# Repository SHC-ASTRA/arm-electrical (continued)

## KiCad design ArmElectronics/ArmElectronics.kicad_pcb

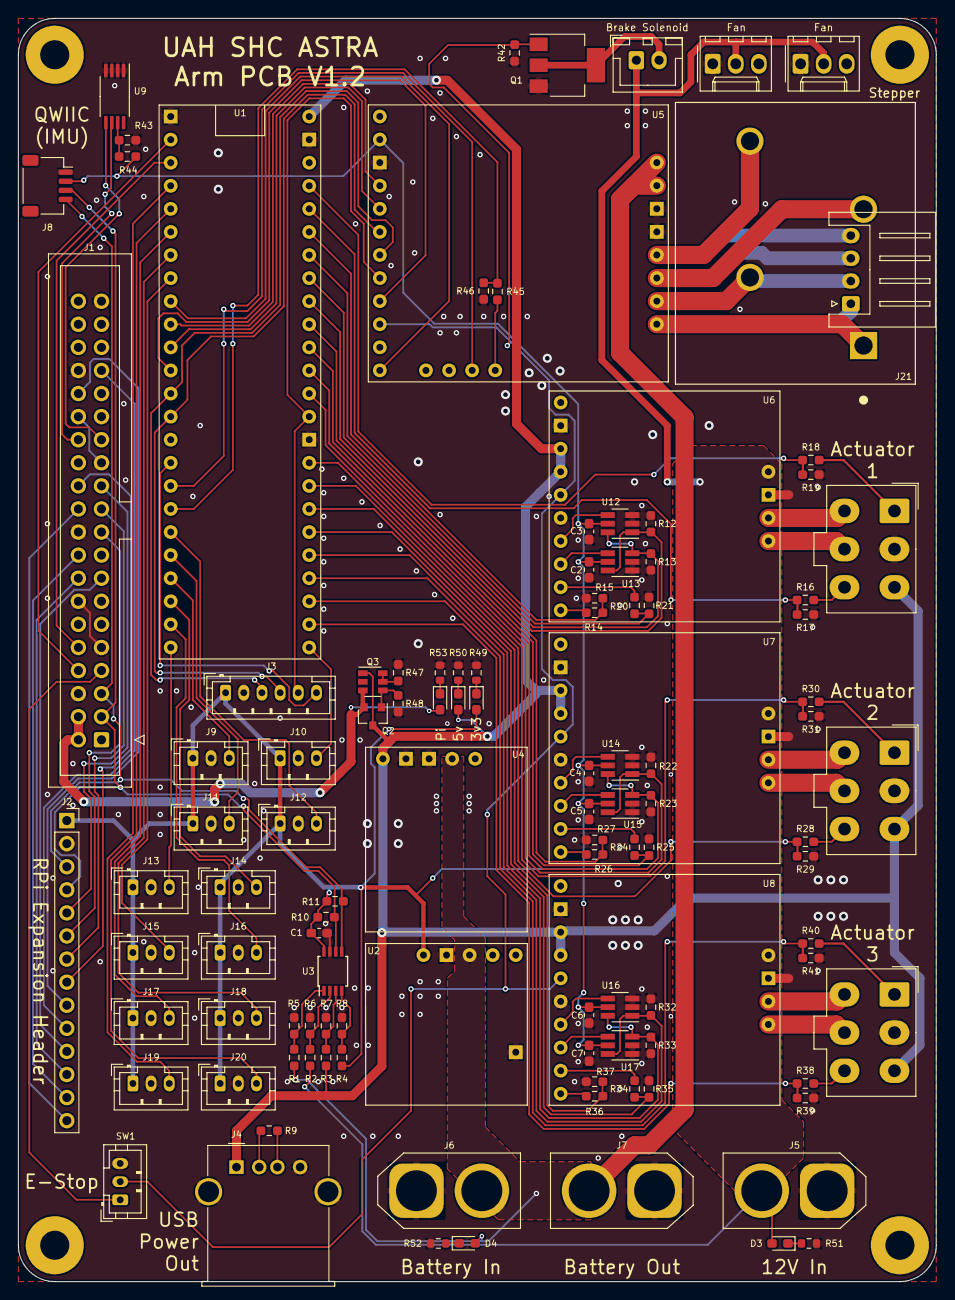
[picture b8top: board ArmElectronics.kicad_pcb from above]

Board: 2 copper layers, 101.0 x 139.0 mm, 116 parts (0 on the bottom side), 108 nets.

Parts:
C1, C2, C3, C4, C5, C6, C7: 0.1u; C_0603_1608Metric_Pad1.05x0.95mm_HandSolder
D1, D2, D3, D4, D5: G; LED_0603_1608Metric_Pad1.05x0.95mm_HandSolder
H1, H2, H3, H4: MountingHole; MountingHole_3.2mm_M3_Pad
J1: Raspberry_Pi_2_3; IDC-Header_2x20_P2.54mm_Vertical
J2: Conn_01x14; PinSocket_1x14_P2.54mm_Vertical
J3: Encoder Breakout; JST_PH_B6B-PH-K_1x06_P2.00mm_Vertical
J4: RasPi Power Out; USB_A_Molex_67643_Horizontal
J5: 12V In; AMASS_XT60-F_1x02_P7.20mm_Vertical
J6: Batt In; AMASS_XT60-F_1x02_P7.20mm_Vertical
J7: Batt Out; AMASS_XT60-F_1x02_P7.20mm_Vertical
J8: BNO055 QWIIC Conn; JST_SH_SM04B-SRSS-TB_1x04-1MP_P1.00mm_Horizontal
J9, J10, J11, J12, J13, J14, J15, J16, J17, J18, J19, J20: AH1815 Breakout; JST_PH_B3B-PH-K_1x03_P2.00mm_Vertical
J21: 1792245; PHOENIX_1792245
J22, J23, J24: PA-09; Molex_Mini-Fit_Jr_5566-06A_2x03_P4.20mm_Vertical
J25: Solenoid; JST_XH_B2B-XH-A_1x02_P2.50mm_Vertical
J26: Stepper Alternate Connection; JST_XH_S4B-XH-A_1x04_P2.50mm_Horizontal
J27, J28: Computer Fan; Molex_KK-254_AE-6410-03A_1x03_P2.54mm_Vertical
Q1: Q_NMOS_GDSD; SOT-223
Q2: Q_PMOS_GSD; SOT-23
Q3: DMMT3906; SOT-23-6
R1: 240k; R_0603_1608Metric_Pad0.98x0.95mm_HandSolder
R2: 62k; R_0603_1608Metric_Pad0.98x0.95mm_HandSolder
R3, R4, R15, R17, R19, R27, R29, R31, R37, R39, R41: 20k; R_0603_1608Metric_Pad0.98x0.95mm_HandSolder
R5, R6, R7, R8, R14, R16, R18, R20, R21, R24, R25, R26, R28, R30, R34, R35, R36, R38, R40, R44, R45, R46, R47: 10k; R_0603_1608Metric_Pad0.98x0.95mm_HandSolder
R9: 200; R_0603_1608Metric_Pad0.98x0.95mm_HandSolder
R10, R11, R12, R13, R22, R23, R32, R33, R42: 100k; R_0603_1608Metric_Pad0.98x0.95mm_HandSolder
R43: DNP; R_0603_1608Metric_Pad0.98x0.95mm_HandSolder
R48: 47k; R_0603_1608Metric_Pad0.98x0.95mm_HandSolder
R49: 10; R_0603_1608Metric
R50, R53: 180; R_0603_1608Metric
R51: 1k; R_0603_1608Metric
R52: 3.3k; R_0603_1608Metric
SW1: E-Stop; JST_PH_B3B-PH-K_1x03_P2.00mm_Vertical
U1: Teensy4.1
U2: Pololu_2857
U3: MAX11607; TSSOP-8_3x3mm_P0.65mm
U4: Pololu_2851
U5: Pololu_3730
U6, U7, U8: TB9051FTG
U9: CAT24C32; TSSOP-8_4.4x3mm_P0.65mm
U12, U13, U14, U15, U16, U17: 74LVC1G97; SOT-23-6_Handsoldering

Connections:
+3V3: C1.2, C2.2, C3.2, C4.2, C5.2, C6.2, C7.2, D1.2, J2.1, J3.1, J8.2, J9.1, J10.1, J11.1, J12.1, J13.1, J14.1, J15.1, J16.1, J17.1, J18.1, J19.1, J20.1, R4.1, R10.2, R11.2, R44.2, U2.5, U3.8, U5.2, U12.5, U13.5, U14.5, U15.5, U16.5, U17.5
+5V: D2.2, J4.1, J22.3, J23.3, J24.3, Q2.3, Q3.1, R3.1, U1.30, U4.5, U6.3, U6.4, U7.3, U7.4, U8.3, U8.4
+12V: D3.2, J5.2, J25.1, J27.2, J28.2, R2.1, U6.15, U7.15, U8.15
+BATT: D4.2, J6.2, J7.2, R1.1, U2.3, U4.2, U5.23, U5.24
/5V_RPI: D5.2, J1.2, J1.4, Q2.2, Q3.3
/Encoder_CS: J3.6, U1.31
/Hall_SW_1: J9.3, U1.36
/Hall_SW_2: J10.3, U1.40
/Hall_SW_3: J11.3, U1.35
/Hall_SW_4: J12.3, U1.34
/Hall_SW_5: J13.3, U1.39
/Hall_SW_6: J14.3, U1.37
/Hall_SW_7: J15.3, U1.8
/Hall_SW_8: J16.3, U1.38
/Hall_SW_9: J17.3, U1.6
/Hall_SW_10: J18.3, U1.7
/Hall_SW_11: J19.3, U1.4
/Hall_SW_12: J20.3, U1.5
/ID_SCL: J1.28, U9.6
/ID_SDA: J1.27, U9.5
/M1_DIAG: R14.2, U6.10
/M1_DIAG_3v: R14.1, R15.2, U1.25
/M1_DIR: R13.2, U1.23, U12.6, U13.3
/M1_HALL1: J22.6, R16.2
/M1_HALL1_3v: R16.1, R17.2, U1.26
/M1_HALL2: J22.1, R18.2
/M1_HALL2_3v: R18.1, R19.2, U1.27
/M1_OCM: R20.2, U6.9
/M1_OCM_3v: R20.1, R21.2, U1.24
/M1_PWM: R12.2, U1.22, U12.1, U13.6
/M1_PWM1: U6.7, U12.4
/M1_PWM2: U6.8, U13.4
/M2_DIAG: R26.2, U7.10
/M2_DIAG_3v: R26.1, R27.2, U1.21
/M2_DIR: R23.2, U1.19, U14.6, U15.3
/M2_HALL1: J23.6, R28.2
/M2_HALL1_3v: R28.1, R29.2, U1.47
/M2_HALL2: J23.1, R30.2
/M2_HALL2_3v: R30.1, R31.2, U1.48
/M2_OCM: R24.2, U7.9
/M2_OCM_3v: R24.1, R25.2, U1.20
/M2_PWM: R22.2, U1.18, U14.1, U15.6
/M2_PWM1: U7.7, U14.4
/M2_PWM2: U7.8, U15.4
/M3_DIAG: R36.2, U8.10
/M3_DIAG_3v: R36.1, R37.2, U1.46
/M3_DIR: R33.2, U1.44, U16.6, U17.3
/M3_HALL1: J24.6, R38.2
/M3_HALL1_3v: R38.1, R39.2, U1.41
/M3_HALL2: J24.1, R40.2
/M3_HALL2_3v: R40.1, R41.2, U1.42
/M3_OCM: R34.2, U8.9
/M3_OCM_3v: R34.1, R35.2, U1.45
/M3_PWM: R32.2, U1.43, U16.1, U17.6
/M3_PWM1: U8.7, U16.4
/M3_PWM2: U8.8, U17.4
/Motor_Enable: J1.7, SW1.1
/RPi_CS0: J1.24, J2.8
/RPi_GPI022: J1.15, J2.11
/RPi_GPIO12: J1.32, J2.9
/RPi_GPIO13: J1.33, J2.10
/RPi_GPIO23: J1.16, J2.12
/RPi_GPIO24: J1.18, J2.13
/RPi_GPIO25: J1.22, J2.14
/RPi_MISO0: J1.21, J2.7
/RPi_MOSI0: J1.19, J2.6
/RPi_RX: J1.10, U1.3
/RPi_SCL: J1.5, J2.3, J8.4, R11.1, U3.5
/RPi_SCLK0: J1.23, J2.5
/RPi_SDA: J1.3, J2.4, J8.3, R10.1, U3.6
/RPi_TX: J1.8, U1.2
/Stepper_BEMF: R45.1, R46.2, U1.33
/Stepper_Dir: U1.11, U5.5
/Stepper_Fault: U1.9, U5.12
/Stepper_Stall: U1.32, U5.15
/Stepper_Step: U1.10, U5.4
/Teensy_CS0: U1.12, U5.9
/Teensy_MISO0: J3.4, U1.14, U5.6
/Teensy_MOSI0: J3.3, U1.13, U5.7
/Teensy_SCK0: J3.5, U1.17, U5.8
/~Disable: Q1.1, R42.2, SW1.2, U5.10, U6.5, U7.5, U8.5
GND: C1.1, C2.1, C3.1, C4.1, C5.1, C6.1, C7.1, J1.6, J1.9, J1.14, J1.20, J1.25, J1.30, J1.34, J1.39, J2.2, J3.2, J4.4, J4.5, J5.1, J6.1, J7.1, J8.1, J9.2, J10.2, J11.2, J12.2, J13.2, J14.2, J15.2, J16.2, J17.2, J18.2, J19.2, J20.2, J22.2, J23.2, J24.2, J27.1, J28.1, Q1.3, R5.2, R6.2, R7.2, R8.2, R12.1, R13.1, R15.1, R17.1, R19.1, R21.1, R22.1, R23.1, R25.1, R27.1, R29.1, R31.1, R32.1, R33.1, R35.1, R37.1, R39.1, R41.1, R42.1, R43.2, R46.1, R47.1, R48.1, R49.2, R50.2, R51.2, R52.2, R53.2, SW1.3, U1.1, U1.16, U1.29, U2.4, U2.6, U3.7, U4.3, U4.4, U5.3, U5.21, U5.22, U6.2, U6.6, U6.16, U7.2, U7.6, U7.16, U8.2, U8.6, U8.16, U9.1, U9.2, U9.3, U9.4, U12.2, U12.3, U13.1, U13.2, U14.2, U14.3, U15.1, U15.2, U16.2, U16.3, U17.1, U17.2
unnamed: D1.1, R49.1
unnamed: D2.1, R50.1
unnamed: D3.1, R51.1
unnamed: D4.1, R52.1
unnamed: D5.1, R53.1
unnamed: J4.2, R9.2
unnamed: J4.3, R9.1
unnamed: J21.1, J26.1, U5.17
unnamed: J21.2, J26.2, U5.18
unnamed: J21.3, J26.3, U5.19
unnamed: J21.4, J26.4, U5.20
unnamed: J22.4, U6.17
unnamed: J22.5, U6.18
unnamed: J23.4, U7.17
unnamed: J23.5, U7.18
unnamed: J24.4, U8.17
unnamed: J24.5, U8.18
unnamed: J25.2, Q1.2, Q1.4
unnamed: Q2.1, Q3.4, R48.2
unnamed: Q3.5, Q3.6, R47.2
unnamed: R1.2, R5.1, U3.1
unnamed: R2.2, R6.1, U3.2
unnamed: R3.2, R7.1, U3.3
unnamed: R4.2, R8.1, U3.4
unnamed: R43.1, R44.1, U9.7
unnamed: R45.2, U5.16

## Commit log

2025-11-04 Add license to readme
2025-11-04 URC '22
2025-11-04 URC '24
2025-11-04 URC '25 - V1
2025-11-04 URC '25 - V2
2025-11-07 PCB Layout....
2025-11-14 Progrss on socket -FeedBack Fixes -PCB Layout and signal routing
2025-11-16 More Work on PCB
    Moved some stuff around
2025-11-18 So Close...
2025-11-20 The Unholy PCB
2026-01-05 Had the plague
2026-01-07 1 PCB 2 PCB 3 PCB ...
2026-01-15 Changes were mostly traces and part spacing
2026-01-20 Optimizations
    Some Labesl
    Mounting Holes
    Changed some pins around for short traces
2026-01-21 Cleaning up things
2026-01-28 Hegale!
    Small optimizations
2026-02-10 Need to swtich to windows
2026-02-15 Moving Connectors and small layout changes
2026-02-26 1/3 Final Changes
2026-03-11 2/3 Final Changes
2026-03-17 Final Part 3
2026-03-30 Details
2026-04-01 Review Changes
2026-04-01 Odering Version
2026-04-03 silk
2026-04-24 fixes for rev 2
2026-05-07 More Changes for REV 2
2026-05-09 Final REV 2 Pt2
